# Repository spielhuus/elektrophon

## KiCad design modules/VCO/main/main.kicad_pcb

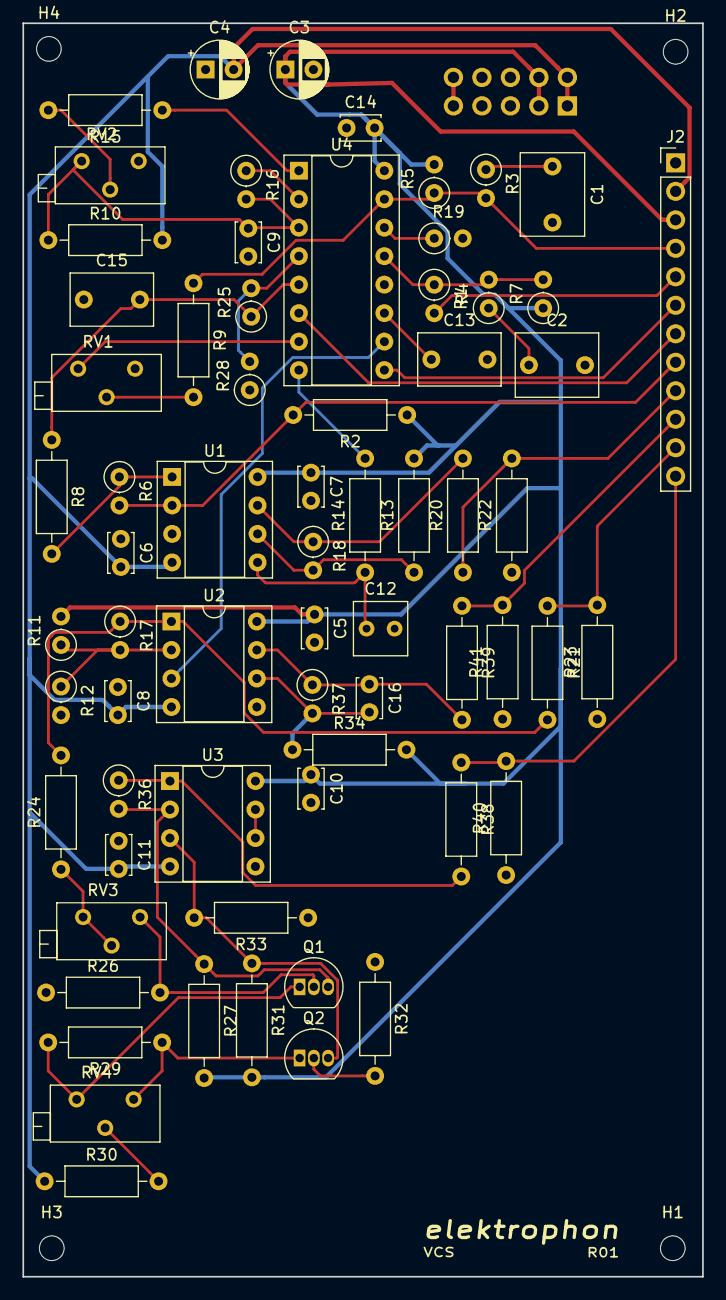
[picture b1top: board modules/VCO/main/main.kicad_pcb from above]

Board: 2 copper layers, 60.6 x 111.8 mm, 72 parts (1 on the bottom side), 46 nets.

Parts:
C1, C2: 0.01u; C_Rect_L7.2mm_W5.5mm_P5.00mm_FKS2_FKP2_MKS2_MKP2
C3, C4: 10u; CP_Radial_D5.0mm_P2.50mm
C5, C6, C7, C8, C9, C10, C11, C14: 0.1u; C_Disc_D3.4mm_W2.1mm_P2.50mm
C12: 33p; C_Rect_L4.6mm_W4.6mm_P2.50mm_MKS02_FKP02
C13: 1000p; C_Rect_L7.2mm_W4.5mm_P5.00mm_FKS2_FKP2_MKS2_MKP2
C15: 0.001u; C_Rect_L7.2mm_W4.5mm_P5.00mm_FKS2_FKP2_MKS2_MKP2
C16: 22p; C_Disc_D3.4mm_W2.1mm_P2.50mm
H1, H2, H3, H4: MountingHole; MountingHole_2.2mm_M2
J1: IDC Header; IDC-Header_2x05_P2.54mm_Vertical
J2: Conn_01x12_Female; PinHeader_1x12_P2.54mm_Vertical
Q1, Q2: 2N3904; TO-92_Inline
R1, R25: 1M; R_Axial_DIN0207_L6.3mm_D2.5mm_P2.54mm_Vertical
R2: 10M; R_Axial_DIN0207_L6.3mm_D2.5mm_P10.16mm_Horizontal
R3, R4: 470; R_Axial_DIN0207_L6.3mm_D2.5mm_P2.54mm_Vertical
R5: 360k; R_Axial_DIN0207_L6.3mm_D2.5mm_P2.54mm_Vertical
R6: 120k; R_Axial_DIN0207_L6.3mm_D2.5mm_P2.54mm_Vertical
R7: 1M5; R_Axial_DIN0207_L6.3mm_D2.5mm_P2.54mm_Vertical
R8, R14, R27, R31: 10k; R_Axial_DIN0207_L6.3mm_D2.5mm_P10.16mm_Horizontal
R9: 1M; R_Axial_DIN0207_L6.3mm_D2.5mm_P10.16mm_Horizontal
R10: 820k; R_Axial_DIN0207_L6.3mm_D2.5mm_P10.16mm_Horizontal
R11: 30k; R_Axial_DIN0207_L6.3mm_D2.5mm_P2.54mm_Vertical
R12, R18, R28: 10k; R_Axial_DIN0207_L6.3mm_D2.5mm_P2.54mm_Vertical
R13, R33: 20k; R_Axial_DIN0207_L6.3mm_D2.5mm_P10.16mm_Horizontal
R15: 24k; R_Axial_DIN0207_L6.3mm_D2.5mm_P10.16mm_Horizontal
R16: 5k6; R_Axial_DIN0207_L6.3mm_D2.5mm_P2.54mm_Vertical
R17: 15k; R_Axial_DIN0207_L6.3mm_D2.5mm_P2.54mm_Vertical
R19: 1k8; R_Axial_DIN0207_L6.3mm_D2.5mm_P2.54mm_Vertical
R20, R21, R41: 1k5; R_Axial_DIN0207_L6.3mm_D2.5mm_P10.16mm_Horizontal
R22, R23: 3k; R_Axial_DIN0207_L6.3mm_D2.5mm_P10.16mm_Horizontal
R24: 47k; R_Axial_DIN0207_L6.3mm_D2.5mm_P10.16mm_Horizontal
R26, R32: 2k2; R_Axial_DIN0207_L6.3mm_D2.5mm_P10.16mm_Horizontal
R29: 390; R_Axial_DIN0207_L6.3mm_D2.5mm_P10.16mm_Horizontal
R30: 18k; R_Axial_DIN0207_L6.3mm_D2.5mm_P10.16mm_Horizontal
R34: 40k; R_Axial_DIN0207_L6.3mm_D2.5mm_P10.16mm_Horizontal
R36: 20k; R_Axial_DIN0207_L6.3mm_D2.5mm_P2.54mm_Vertical
R37: 33k; R_Axial_DIN0207_L6.3mm_D2.5mm_P2.54mm_Vertical
R38, R40: 2k; R_Axial_DIN0207_L6.3mm_D2.5mm_P10.16mm_Horizontal
R39: 2k26; R_Axial_DIN0207_L6.3mm_D2.5mm_P10.16mm_Horizontal
RV1, RV2: 10k; Potentiometer_Bourns_3296Z_Horizontal
RV3, RV4: 50k; Potentiometer_Bourns_3296Z_Horizontal
U1, U2, U3: TL072; DIP-8_W7.62mm_Socket
U4: CEM3340; DIP-16_W7.62mm_Socket

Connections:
+5V: J1.9, J1.10
+15V: C3.1, C5.1, C7.1, C10.1, C14.2, J1.3, J1.4, J2.3, R2.1, R5.2, R7.1, R11.2, R13.2, R27.2, R31.2, R34.2, U1.8, U2.8, U3.8, U4.16
-15V: C4.2, C6.2, C8.2, C11.2, J1.1, J1.2, J2.2, R10.2, R30.1, U1.4, U2.4, U3.4
/CV: J2.4, R3.2, R5.1, R9.1, U4.15
/HARD_SYNC: J2.7, U4.6
/HF_Trim: RV1.3, U4.7
/IN_LIN_FM: J2.5, R1.2
/IN_PWM: J2.8, R2.2, R6.2, U1.2
/LIN_FM: R1.1, R4.2, R7.2, U4.13
/PULSE: J2.10, R39.1, R41.2
/PULSE_RAW: R25.2, R28.2, U2.5, U4.4
/PWM: C15.2, R8.1, R25.1, U4.5
/SAW: J2.9, R20.1, R22.2
/SAW_RAW: R14.2, U4.8
/SINE: J2.12, R38.1, R40.2
/SOFT_SYNC: J2.6, U4.9
/TRIANGLE: J2.11, R21.1, R23.2
/TRI_RAW: U2.3, U4.10
GND: C1.2, C2.2, C3.2, C4.1, C5.2, C6.1, C7.2, C8.1, C9.2, C10.2, C11.1, C12.2, C13.2, C14.1, C15.1, J1.5, J1.6, J1.7, J1.8, J2.1, R12.2, R19.2, R22.1, R23.1, R26.1, R28.1, R32.1, R33.1, R40.1, R41.1, RV1.1, U1.3, U3.5, U4.12
unnamed: C1.1, R3.1
unnamed: C2.1, R4.1
unnamed: C9.1, R10.1, R16.2, RV2.3, U4.3
unnamed: C12.1, R14.1, U1.5
unnamed: C13.1, U4.11
unnamed: C16.1, R37.1, R39.2, U2.7
unnamed: C16.2, R34.1, R37.2, U2.6
unnamed: Q1.1, R29.2, RV4.3
unnamed: Q1.2, R26.2, RV3.1
unnamed: Q1.3, R27.1, R36.2, U3.2
unnamed: Q2.1, R29.1, RV4.1
unnamed: Q2.2, R32.2
unnamed: Q2.3, R31.1, R33.2, U3.3
unnamed: R6.1, R8.2, U1.1
unnamed: R9.2, RV1.2
unnamed: R11.1, R12.1, R17.2, U2.2
unnamed: R13.1, R18.2, U1.6
unnamed: R15.1, U4.1
unnamed: R15.2, RV2.2
unnamed: R16.1, U4.2
unnamed: R17.1, R21.2, R24.2, U2.1
unnamed: R18.1, R20.2, U1.7
unnamed: R19.1, U4.14
unnamed: R24.1, RV3.2, RV3.3
unnamed: R30.2, RV4.2
unnamed: R36.1, R38.2, U3.1
unnamed: U3.6, U3.7

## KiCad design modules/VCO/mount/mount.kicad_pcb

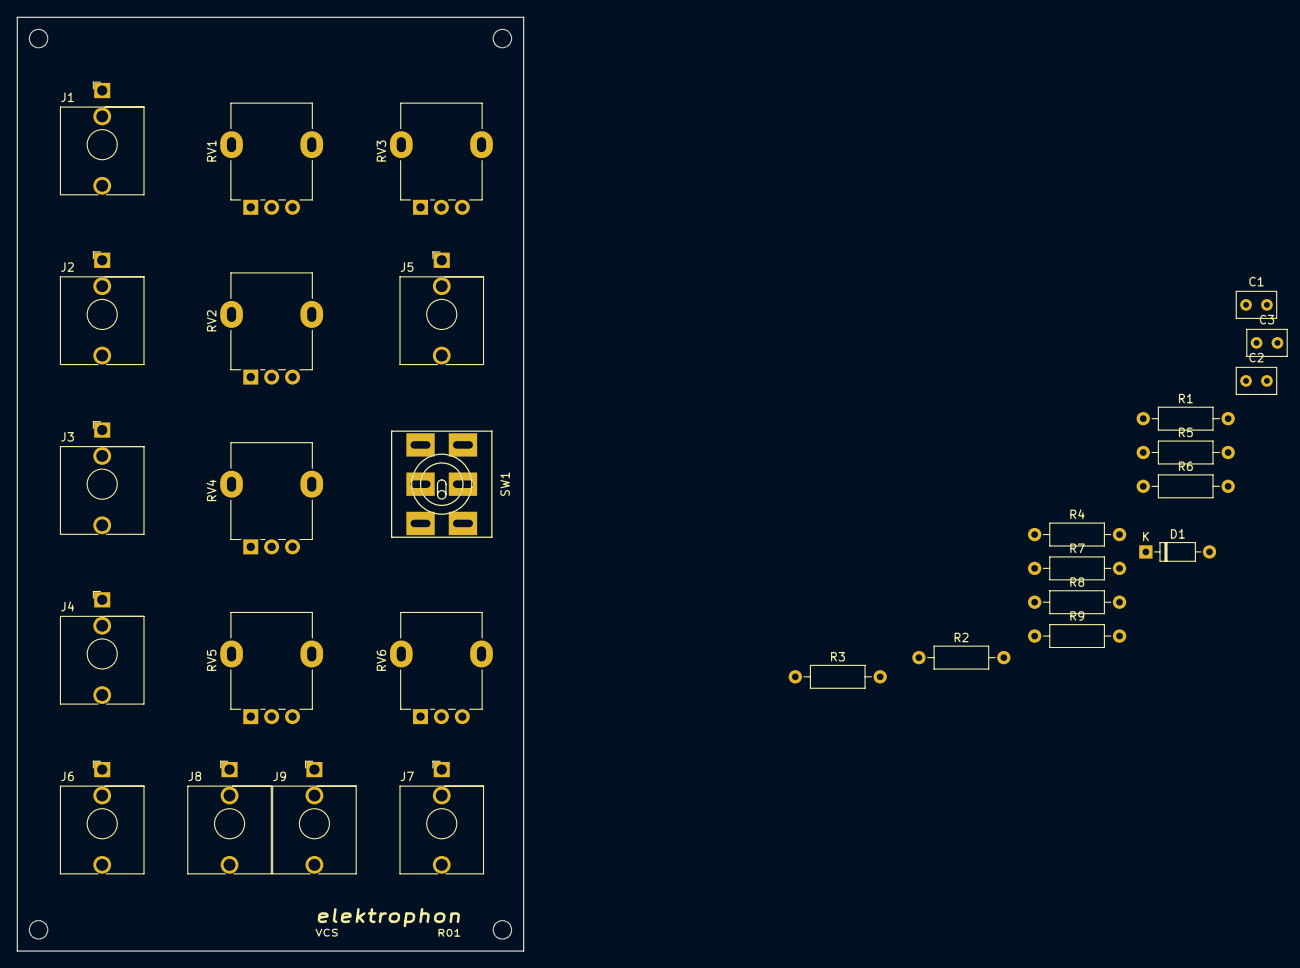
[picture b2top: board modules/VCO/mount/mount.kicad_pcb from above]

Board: 2 copper layers, 60.6 x 111.8 mm, 33 parts (0 on the bottom side), 22 nets, no tracks yet.

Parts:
C1: 0.22u; C_Rect_L4.6mm_W3.0mm_P2.50mm_MKS02_FKP02
C2: 0.001u; C_Rect_L4.6mm_W3.0mm_P2.50mm_MKS02_FKP02
C3: 0.1u; C_Rect_L4.6mm_W3.0mm_P2.50mm_MKS02_FKP02
D1: 1N4148; D_DO-35_SOD27_P7.62mm_Horizontal
H1, H2, H3, H4: MountingHole; MountingHole_2.2mm_M2
J1, J2, J3, J4, J5, J6, J7, J8, J9: AudioJack2_SwitchT; Jack_3.5mm_WQP-PJ301BM_Vertical
R1, R2, R4, R6: 100k; R_Axial_DIN0207_L6.3mm_D2.5mm_P10.16mm_Horizontal
R3: 3M3; R_Axial_DIN0207_L6.3mm_D2.5mm_P10.16mm_Horizontal
R5: 47k; R_Axial_DIN0207_L6.3mm_D2.5mm_P10.16mm_Horizontal
R7: 300k; R_Axial_DIN0207_L6.3mm_D2.5mm_P10.16mm_Horizontal
R8: 5k6; R_Axial_DIN0207_L6.3mm_D2.5mm_P10.16mm_Horizontal
R9: 10k; R_Axial_DIN0207_L6.3mm_D2.5mm_P10.16mm_Horizontal
RV1, RV2, RV3, RV4, RV5, RV6: 100k; Potentiometer_Alpha_RD901F-40-00D_Single_Vertical
SW1: SW_DPDT_x2; Tumbler_SW_x2

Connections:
+15V: RV2.3, RV3.3, RV6.3
-15V: RV2.1, RV3.1
GND: C3.2, J1.S, J2.S, J3.S, J4.S, J5.S, J6.S, J7.S, J8.S, J9.S, R9.1, RV1.1, RV4.1, RV5.1, RV6.1
unnamed: C1.1, J3.T
unnamed: C1.2, RV4.3
unnamed: C2.1, J5.T
unnamed: C2.2, SW1.2
unnamed: C3.1, SW1.6
unnamed: D1.1, R8.1, R9.2
unnamed: J1.T, RV1.3
unnamed: J2.T, R4.2
unnamed: J4.T, RV5.3
unnamed: R1.1, R2.1, R3.1, R4.1
unnamed: R1.2, RV1.2
unnamed: R2.2, RV2.2
unnamed: R3.2, RV3.2
unnamed: R5.1, SW1.5
unnamed: R6.1, R7.1
unnamed: R6.2, RV5.2
unnamed: R7.2, RV6.2
unnamed: R8.2, SW1.3
unnamed: SW1.1, SW1.4

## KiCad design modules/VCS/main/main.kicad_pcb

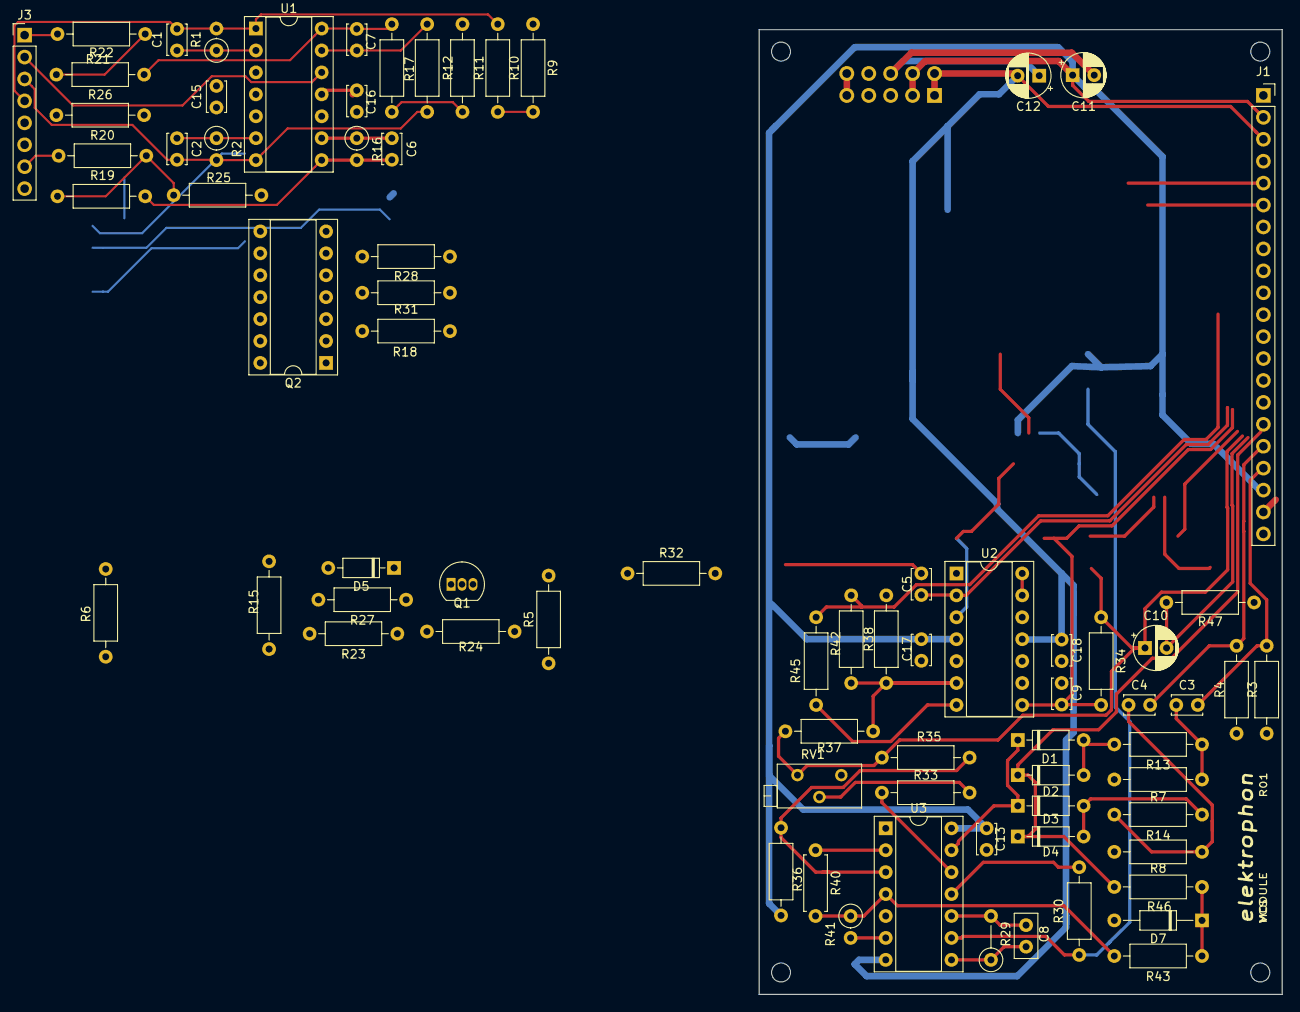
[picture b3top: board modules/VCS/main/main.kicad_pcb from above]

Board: 2 copper layers, 60.6 x 111.8 mm, 81 parts (1 on the bottom side), 55 nets.

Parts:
C1, C2, C5, C6, C7: 47p; C_Disc_D3.4mm_W2.1mm_P2.50mm
C3, C4: 1n; C_Disc_D3.4mm_W2.1mm_P2.50mm
C8: 47p; C_Disc_D5.0mm_W2.5mm_P2.50mm
C9: 22n; C_Disc_D3.4mm_W2.1mm_P2.50mm
C10: 47u; CP_Radial_D5.0mm_P2.50mm
C11, C12: 10u; CP_Radial_D5.0mm_P2.50mm
C13, C15, C16, C17, C18: 0.1u; C_Disc_D3.4mm_W2.1mm_P2.50mm
D1, D2, D3, D4, D5: 1N4148; D_DO-35_SOD27_P7.62mm_Horizontal
D7: 5v5; D_DO-35_SOD27_P10.16mm_Horizontal
H1, H2, H3, H4: MountingHole; MountingHole_2.2mm_M2
J1: Conn_01x21_Female; PinSocket_1x21_P2.54mm_Vertical
J2: IDC Header; IDC-Header_2x05_P2.54mm_Vertical
J3: Conn_01x08_Female; PinHeader_1x08_P2.54mm_Vertical
Q1: 2N3906; TO-92_Inline
Q2: THAT340; DIP-14_W7.62mm_Socket
R1, R2: 100k; R_Axial_DIN0207_L6.3mm_D2.5mm_P2.54mm_Vertical
R3, R4, R5, R6, R7, R8, R37, R42: 100k; R_Axial_DIN0207_L6.3mm_D2.5mm_P10.16mm_Horizontal
R9, R11, R47: 1M; R_Axial_DIN0207_L6.3mm_D2.5mm_P10.16mm_Horizontal
R10, R12: 470k; R_Axial_DIN0207_L6.3mm_D2.5mm_P10.16mm_Horizontal
R13, R14: 33k; R_Axial_DIN0207_L6.3mm_D2.5mm_P10.16mm_Horizontal
R15: 10M; R_Axial_DIN0207_L6.3mm_D2.5mm_P10.16mm_Horizontal
R16: 820k; R_Axial_DIN0207_L6.3mm_D2.5mm_P2.54mm_Vertical
R17, R30: 820k; R_Axial_DIN0207_L6.3mm_D2.5mm_P10.16mm_Horizontal
R18: 8k2; R_Axial_DIN0207_L6.3mm_D2.5mm_P10.16mm_Horizontal
R19, R20, R21, R22, R28: 82k; R_Axial_DIN0207_L6.3mm_D2.5mm_P10.16mm_Horizontal
R23, R27, R32, R33: 220k; R_Axial_DIN0207_L6.3mm_D2.5mm_P10.16mm_Horizontal
R24: 68k; R_Axial_DIN0207_L6.3mm_D2.5mm_P10.16mm_Horizontal
R25, R26, R43: 2k2; R_Axial_DIN0207_L6.3mm_D2.5mm_P10.16mm_Horizontal
R29: 820k; R_Axial_DIN0207_L6.3mm_D2.5mm_P5.08mm_Vertical
R31: 1k8; R_Axial_DIN0207_L6.3mm_D2.5mm_P10.16mm_Horizontal
R34: 100; R_Axial_DIN0207_L6.3mm_D2.5mm_P10.16mm_Horizontal
R35: 330k; R_Axial_DIN0207_L6.3mm_D2.5mm_P10.16mm_Horizontal
R36: 10m; R_Axial_DIN0207_L6.3mm_D2.5mm_P10.16mm_Horizontal
R38: 620k; R_Axial_DIN0207_L6.3mm_D2.5mm_P10.16mm_Horizontal
R40: 1m; R_Axial_DIN0207_L6.3mm_D2.5mm_P7.62mm_Horizontal
R41: 1m; R_Axial_DIN0207_L6.3mm_D2.5mm_P2.54mm_Vertical
R45: 330; R_Axial_DIN0207_L6.3mm_D2.5mm_P10.16mm_Horizontal
R46: 1k; R_Axial_DIN0207_L6.3mm_D2.5mm_P10.16mm_Horizontal
RV1: 100k; Potentiometer_Bourns_3296Z_Horizontal
U1, U2: TL074; DIP-14_W7.62mm_Socket
U3: LM3900; DIP-14_W7.62mm_Socket

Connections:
+5V: J2.9, J2.10
+15V: C11.1, C13.1, C13.2, C15.1, C15.2, C16.1, C17.1, C17.2, C18.1, J1.2, J2.3, J2.4, Q1.1, R24.1, R36.1, U1.4, U2.4, U3.7, U3.14
-15V: C12.2, C16.2, C18.2, J1.3, J2.1, J2.2, R27.2, U1.11, U2.11
/AC_OUT: C10.2, J1.18, R47.1
/BIPOLAR_OUT: J1.14, R42.2, R45.2
/CV: J1.13, R28.1
/CYCLE_1: C4.2, J1.20, R4.2
/CYCLE_2: D2.1, D4.1, J1.19, R46.1
/FALL: C1.1, J3.5, R1.1, U1.2
/FALL_1: C1.2, J3.4, R1.2, R10.1, U1.1
/FALL_2: J3.6, U1.10
/FALL_RATE: J3.7, R20.1
/IN: J1.9, R5.2, R6.1
/NET_1: C9.2, J1.15, R32.2, R34.1, U2.8
/OUT: C10.1, J1.17, R34.2, R35.2, R37.1, RV1.3
/RISE: C2.1, J3.8, R2.1, U1.6
/RISE_1: C2.2, J3.3, R2.2, R12.1, U1.7
/RISE_2: J3.2, U1.12
/RISE_RATE: J3.1, R22.1
/TRIGGER: C3.2, J1.21, R3.2
GND: C11.2, C12.1, D7.2, J1.1, J2.5, J2.6, J2.7, J2.8, Q2.1, Q2.4, Q2.7, Q2.11, R3.1, R4.1, R5.1, R7.1, R8.1, R9.1, R11.1, R25.2, R26.2, R31.2, R38.1, R47.2, RV1.1, U1.3, U1.5, U2.5, U2.10, U2.12, U3.1
unnamed: C3.1, R7.2, R13.1
unnamed: C4.1, R8.2, R14.1
unnamed: C5.1, R15.1
unnamed: C5.2, R6.2, U2.2
unnamed: C6.1, R9.2, R10.2, R16.1, U1.9
unnamed: C6.2, R16.2, R19.1, U1.8
unnamed: C7.1, R11.2, R12.2, R17.1, U1.13
unnamed: C7.2, R17.2, R21.1, U1.14
unnamed: C8.1, R29.1, U3.8
unnamed: C8.2, R29.2, U3.10
unnamed: C9.1, Q2.8, Q2.14, U2.9
unnamed: D1.1, D3.1, U3.13
unnamed: D1.2, D2.2, R13.2
unnamed: D3.2, D4.2, R14.2
unnamed: D5.1, Q1.3, R27.1
unnamed: D5.2, R32.1, U2.3
unnamed: D7.1, R43.1, R46.2
unnamed: Q1.2, R23.2, R24.2
unnamed: Q2.2, R21.2, R22.2, R26.1
unnamed: Q2.9, R19.2, R20.2, R25.1
unnamed: Q2.3, Q2.5, Q2.10, Q2.12, R18.2
unnamed: Q2.6, Q2.13, R28.2, R31.1
unnamed: R15.2, R18.1, U2.1
unnamed: R30.2, U3.11
unnamed: R33.1, U3.12
unnamed: R33.2, RV1.2
unnamed: R35.1, R36.2, U3.3
unnamed: R37.2, R38.2, R42.1, U2.6
unnamed: R40.1, R41.1, R43.2, U3.4
unnamed: R40.2, U3.2
unnamed: R41.2, U3.6
unnamed: R45.1, U2.7
unnamed: U2.13, U2.14
TRIG: R23.1, R30.1, U3.9

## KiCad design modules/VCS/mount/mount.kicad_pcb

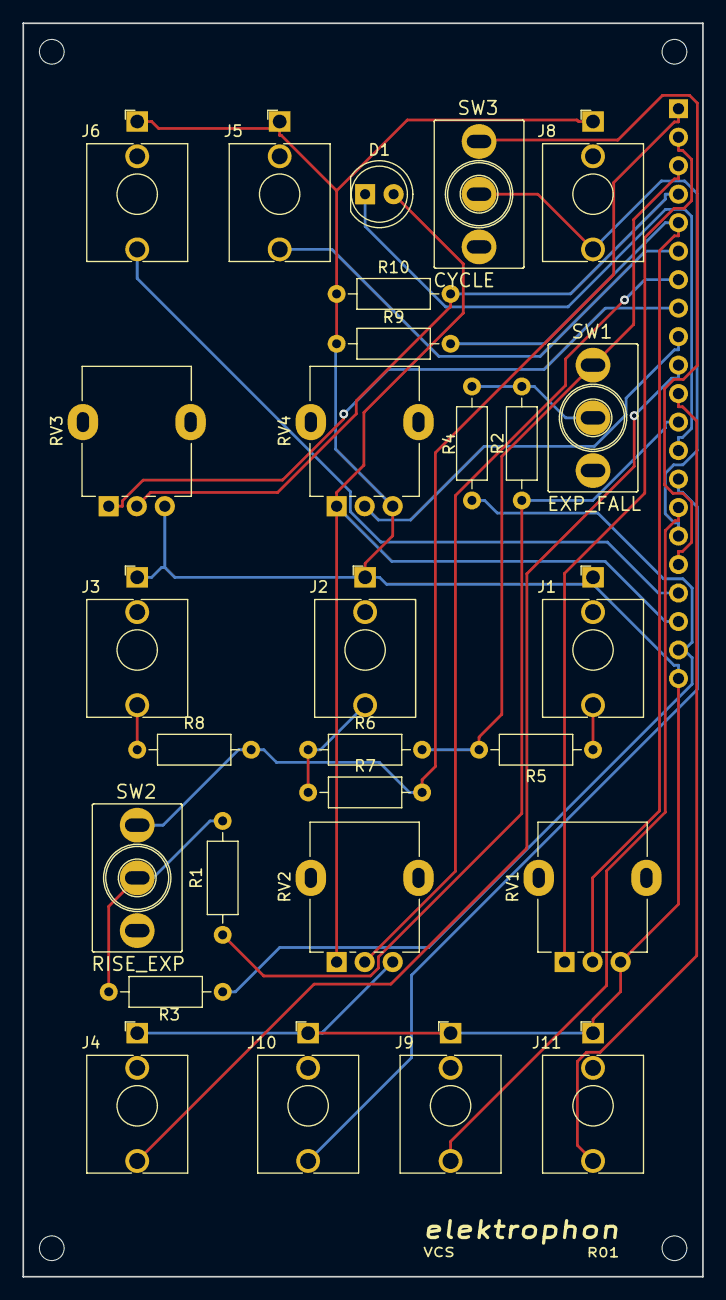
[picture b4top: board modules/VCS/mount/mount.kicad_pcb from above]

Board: 2 copper layers, 60.6 x 111.8 mm, 33 parts (1 on the bottom side), 26 nets.

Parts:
D1: LED; LED_D5.0mm_Clear
H1, H2, H3, H4: MountingHole; MountingHole_2.2mm_M2
J1: FALL CV; Jack_3.5mm_QingPu_WQP-PJ398SM_Vertical_CircularHoles
J2: BOTH CV; Jack_3.5mm_QingPu_WQP-PJ398SM_Vertical_CircularHoles
J3: RISE CV; Jack_3.5mm_QingPu_WQP-PJ398SM_Vertical_CircularHoles
J4: CV (1V/OCT); Jack_3.5mm_QingPu_WQP-PJ398SM_Vertical_CircularHoles
J5: IN; Jack_3.5mm_QingPu_WQP-PJ398SM_Vertical_CircularHoles
J6: TRIGGER; Jack_3.5mm_QingPu_WQP-PJ398SM_Vertical_CircularHoles
J7: Conn_01x21_Male; PinHeader_1x21_P2.54mm_Vertical
J8: END; Jack_3.5mm_QingPu_WQP-PJ398SM_Vertical_CircularHoles
J9: AC OUT; Jack_3.5mm_QingPu_WQP-PJ398SM_Vertical_CircularHoles
J10: OUT; Jack_3.5mm_QingPu_WQP-PJ398SM_Vertical_CircularHoles
J11: BIPOLAR OUT; Jack_3.5mm_QingPu_WQP-PJ398SM_Vertical_CircularHoles
R1, R2: 330k; R_Axial_DIN0207_L6.3mm_D2.5mm_P10.16mm_Horizontal
R3, R4, R9, R10: 1M; R_Axial_DIN0207_L6.3mm_D2.5mm_P10.16mm_Horizontal
R5, R6, R7, R8: 100k; R_Axial_DIN0207_L6.3mm_D2.5mm_P10.16mm_Horizontal
RV1, RV3: 50k; Potentiometer_Alpha_RD901F-40-00D_Single_Vertical
RV2, RV4: 100k; Potentiometer_Alpha_RD901F-40-00D_Single_Vertical
SW1: EXP_FALL; SPDT_KIT
SW2: RISE_EXP; SPDT_KIT
SW3: CYCLE; SPDT_KIT

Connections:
+15V: D1.2, J7.19, RV2.1, RV4.1
-15V: J7.20, R3.2, R4.2
/AC_OUT: J7.15, J9.T
/BIPOLAR_OUT: J7.11, J11.T
/CV: J4.T, J7.10
/CYCLE_1: J7.17, SW3.1
/CYCLE_2: J7.16, J8.T, SW3.2
/FALL: J7.3, R5.2, R6.2, SW1.1
/FALL_1: J7.2, RV1.1
/FALL_2: J7.5, R9.2, RV1.2
/FALL_RATE: J7.7, RV2.2
/IN: J5.T, J7.6
/LED: D1.1, J7.13
/NET_1: J7.12, R1.1, R2.1
/OUT: J7.14, J10.T
/RISE: J7.1, R7.2, R8.2, SW2.1
/RISE_1: J7.8, RV3.1
/RISE_2: J7.4, R10.2, RV3.2
/RISE_RATE: J7.9, RV4.2
/TRIGGER: J6.T, J7.18
GND: J1.S, J2.S, J3.S, J4.S, J5.S, J6.S, J7.21, J8.S, J9.S, J10.S, J11.S, R9.1, R10.1, RV1.3, RV2.3, RV3.3, RV4.3
unnamed: J1.T, R5.1
unnamed: J2.T, R6.1, R7.1
unnamed: J3.T, R8.1
unnamed: R1.2, R3.1, SW2.2
unnamed: R2.2, R4.1, SW1.2

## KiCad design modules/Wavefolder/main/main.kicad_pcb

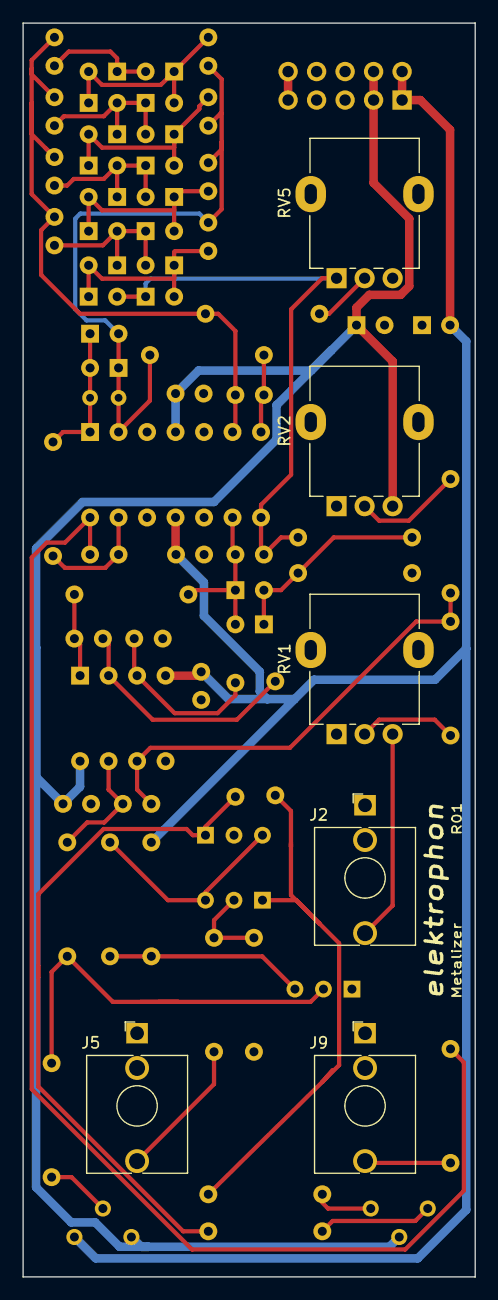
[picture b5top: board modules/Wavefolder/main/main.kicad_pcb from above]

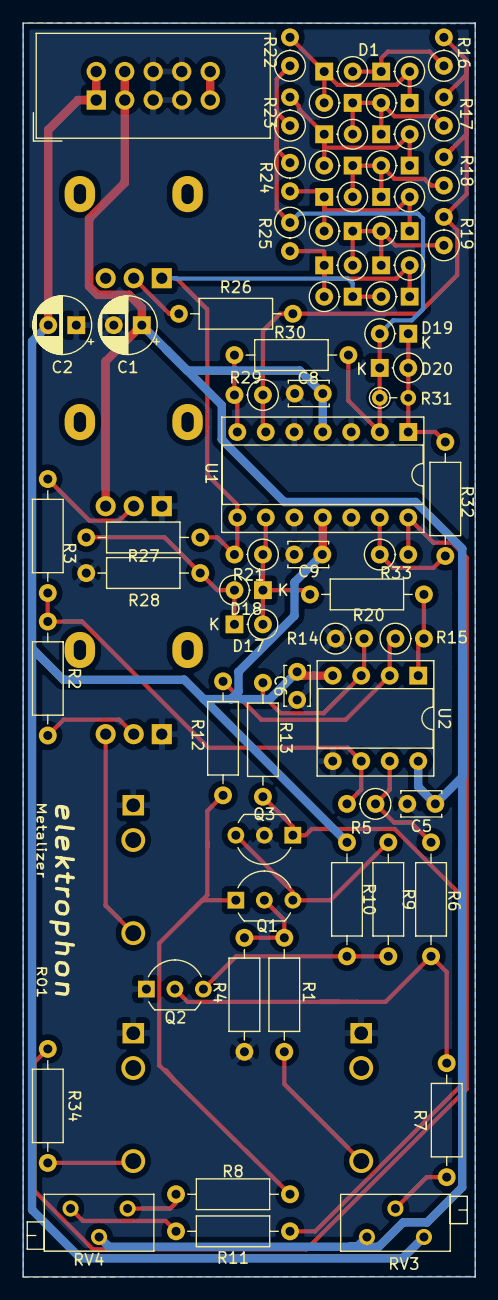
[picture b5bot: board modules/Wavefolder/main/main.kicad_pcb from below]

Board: 2 copper layers, 40.3 x 111.8 mm, 74 parts (68 on the bottom side), 41 nets.

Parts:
C1, C2: 10u; CP_Radial_D5.0mm_P2.50mm
C5, C6, C8, C9: 0.1u; C_Disc_D3.4mm_W2.1mm_P2.50mm
D1, D2, D3, D4, D5, D6, D7, D8, D9, D10, D11, D12, D13, D14, D15, D16, D17, D18, D19, D20: D; D_DO-35_SOD27_P2.54mm_Vertical_KathodeUp
J2: Control; Jack_3.5mm_WQP-PJ398SM_Vertical
J5: INPUT; Jack_3.5mm_WQP-PJ398SM_Vertical
J6: POWER; IDC-Header_2x05_P2.54mm_Vertical
J9: OUT; Jack_3.5mm_WQP-PJ398SM_Vertical
Q1, Q2, Q3: BC547; TO-92_Inline_Wide
R1, R3, R20: 100k; R_Axial_DIN0207_L6.3mm_D2.5mm_P10.16mm_Horizontal
R2: 68k; R_Axial_DIN0207_L6.3mm_D2.5mm_P10.16mm_Horizontal
R4: 680; R_Axial_DIN0207_L6.3mm_D2.5mm_P10.16mm_Horizontal
R5, R14, R15, R21: 100k; R_Axial_DIN0207_L6.3mm_D2.5mm_P2.54mm_Vertical
R6, R7: 22k; R_Axial_DIN0207_L6.3mm_D2.5mm_P10.16mm_Horizontal
R8, R10, R11: 15k; R_Axial_DIN0207_L6.3mm_D2.5mm_P10.16mm_Horizontal
R9, R27: 33k; R_Axial_DIN0207_L6.3mm_D2.5mm_P10.16mm_Horizontal
R12, R13: 10k; R_Axial_DIN0207_L6.3mm_D2.5mm_P10.16mm_Horizontal
R16, R17, R18, R19, R22, R23, R24, R25: 15k; R_Axial_DIN0207_L6.3mm_D2.5mm_P2.54mm_Vertical
R26: 27k; R_Axial_DIN0207_L6.3mm_D2.5mm_P10.16mm_Horizontal
R28: 2k7; R_Axial_DIN0207_L6.3mm_D2.5mm_P10.16mm_Horizontal
R29: 5k6; R_Axial_DIN0207_L6.3mm_D2.5mm_P2.54mm_Vertical
R30: 5k6; R_Axial_DIN0207_L6.3mm_D2.5mm_P10.16mm_Horizontal
R31: 56k; R_Axial_DIN0204_L3.6mm_D1.6mm_P2.54mm_Vertical
R32: 6k8; R_Axial_DIN0207_L6.3mm_D2.5mm_P10.16mm_Horizontal
R33: 56k; R_Axial_DIN0207_L6.3mm_D2.5mm_P2.54mm_Vertical
R34: 470; R_Axial_DIN0207_L6.3mm_D2.5mm_P10.16mm_Horizontal
RV1, RV2: 100k; Potentiometer_Alpha_RD901F-40-00D_Single_Vertical
RV3: 50k; Potentiometer_Bourns_3296Z_Horizontal
RV4: 1k; Potentiometer_Bourns_3296Z_Horizontal
RV5: 47k; Potentiometer_Alpha_RD901F-40-00D_Single_Vertical
U1: TL074; DIP-14_W7.62mm_Socket
U2: TL072; DIP-8_W7.62mm_Socket

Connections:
+5V: J6.9, J6.10
+15V: C1.1, C5.1, C8.1, J6.3, J6.4, RV2.3, RV3.1, RV4.2, U1.4, U2.8
-15V: C2.2, C6.2, C9.2, J6.1, J6.2, R10.1, RV3.3, U1.11, U2.4
GND: C1.2, C2.1, C5.2, C6.1, C8.2, C9.1, J2.S, J5.S, J6.5, J6.6, J6.7, J6.8, J9.S, Q2.1, Q3.2, R4.1, R14.1, R28.1, RV1.1, RV2.1, U1.3, U1.5, U1.10, U1.12, U2.5
unnamed: D1.1, D9.2, R16.1
unnamed: D1.2, D2.1, D9.1, D10.2, R22.2
unnamed: D2.2, D3.1, D10.1, D11.2, R17.1
unnamed: D3.2, D4.1, D11.1, D12.2, R23.2
unnamed: D4.2, D5.1, D12.1, D13.2, R18.1
unnamed: D5.2, D6.1, D13.1, D14.2, R24.2
unnamed: D6.2, D7.1, D14.1, D15.2, R19.1
unnamed: D7.2, D8.1, D15.1, D16.2, R25.2
unnamed: D8.2, D16.1, R21.2, R27.1, RV5.1, U1.8
unnamed: D17.1, D18.2, R27.2, R28.2
unnamed: D17.2, D18.1, R20.2, R21.1, U1.9
unnamed: D19.1, D20.2, R31.2, R32.1, U1.1
unnamed: D19.2, D20.1, R22.1, R23.1, R24.1, R25.1, R30.2, R31.1, U1.2
unnamed: J2.T, RV1.3
unnamed: J5.T, R1.2
unnamed: J9.T, R34.2
unnamed: Q1.1, R8.1, R12.2
unnamed: Q1.2, R1.1, R4.2
unnamed: Q1.3, Q3.3, R9.2
unnamed: Q2.2, R6.1, R7.2
unnamed: Q2.3, R9.1, R10.2
unnamed: Q3.1, R11.1, R13.2
unnamed: R2.1, R3.1, R5.2, U2.6
unnamed: R2.2, RV1.2
unnamed: R3.2, RV2.2
unnamed: R5.1, R6.2, U2.7
unnamed: R7.1, RV3.2
unnamed: R8.2, RV4.1
unnamed: R11.2, RV4.3
unnamed: R12.1, R15.1, U2.2
unnamed: R13.1, R14.2, U2.3
unnamed: R15.2, R20.1, U2.1
unnamed: R16.2, R17.2, R18.2, R19.2, R26.2, R29.1, U1.6
unnamed: R26.1, RV5.2
unnamed: R29.2, R30.1, U1.7
unnamed: R32.2, R33.1, U1.13
unnamed: R33.2, R34.1, U1.14

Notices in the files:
modules/VCO/main/main.kicad_pcb:
License CC BY 4.0 - Attribution 4.0 International
